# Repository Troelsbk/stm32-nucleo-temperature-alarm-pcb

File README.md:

# STM32 Nucleo Temperature Alarm

## Overview
This project demonstrates a temperature alarm system built on the STM32 Nucleo F042K6 platform with a custom PCB designed in KiCad.  
It integrates multiple I/O types, including I²C, ADC with interrupts, PWM, GPIO buttons, and LEDs.  
The system activates an alarm when the measured temperature falls below a user-defined threshold.  
A potential application is monitoring room temperature when ventilating by opening windows.

## Hardware
- STM32 Nucleo F042K6 development board  
- Custom PCB designed in KiCad  
- Analog temperature sensor TMP36  
- Digital temperature sensor TMP102  
- Push buttons for setting the threshold  
- Buzzer for alarm output  
- OLED display  
- Status LEDs  

### System Overview

### OLED
This project uses the [stm32-ssd1306] library to drive the OLED display.  
In addition, three helper functions were implemented to simplify text rendering on the OLED.  
These functions are defined in `oled_function.c`:

- `void send_strXY(char *str, uint8_t x, uint8_t y, uint8_t size);`  
- `char send_charXY(char ch, uint8_t x, uint8_t y);`  
- `void clear_oled(void);`  

### Schematic
The schematic designed in KiCad is shown below:  

### Breadboard Prototype

## Firmware
The firmware was developed using STM32CubeIDE.  
It is available in the [`stm32_firmware/`](./stm32_firmware) folder.  
To rebuild the project:  
1. Open the `.ioc` configuration file in STM32CubeMX.  
2. Regenerate the source code.  
3. Compile using STM32CubeIDE or a compatible ARM toolchain.  

## PCB
### Layout

### 3D Model

### Assembled PCB
The fully assembled PCB is shown below.  
The green LED indicates that the I²C bus is operational.  
The red LED flashes, and the buzzer sounds, when the temperature measured by the TMP102 falls below the user-defined threshold.

### PCB Performance
The analog TMP36 sensor showed a deviation of 0–3 °C above the reference, while the TMP102 measured about 1 °C higher.  
Aside from these temperature discrepancies, the PCB performed as expected.

## Demo Video

## Summary
Overall, the project achieved its primary goal of providing hands-on experience with KiCad, as well as STM32 features including ADC with interrupts, timers, I²C, PWM, GPIO, and OLED display integration.  
This made it a valuable learning and familiarization exercise with the STM32 Nucleo ecosystem.

## License
MIT License (or another license of your choice).

[stm32-ssd1306]: https://github.com/afiskon/stm32-ssd1306

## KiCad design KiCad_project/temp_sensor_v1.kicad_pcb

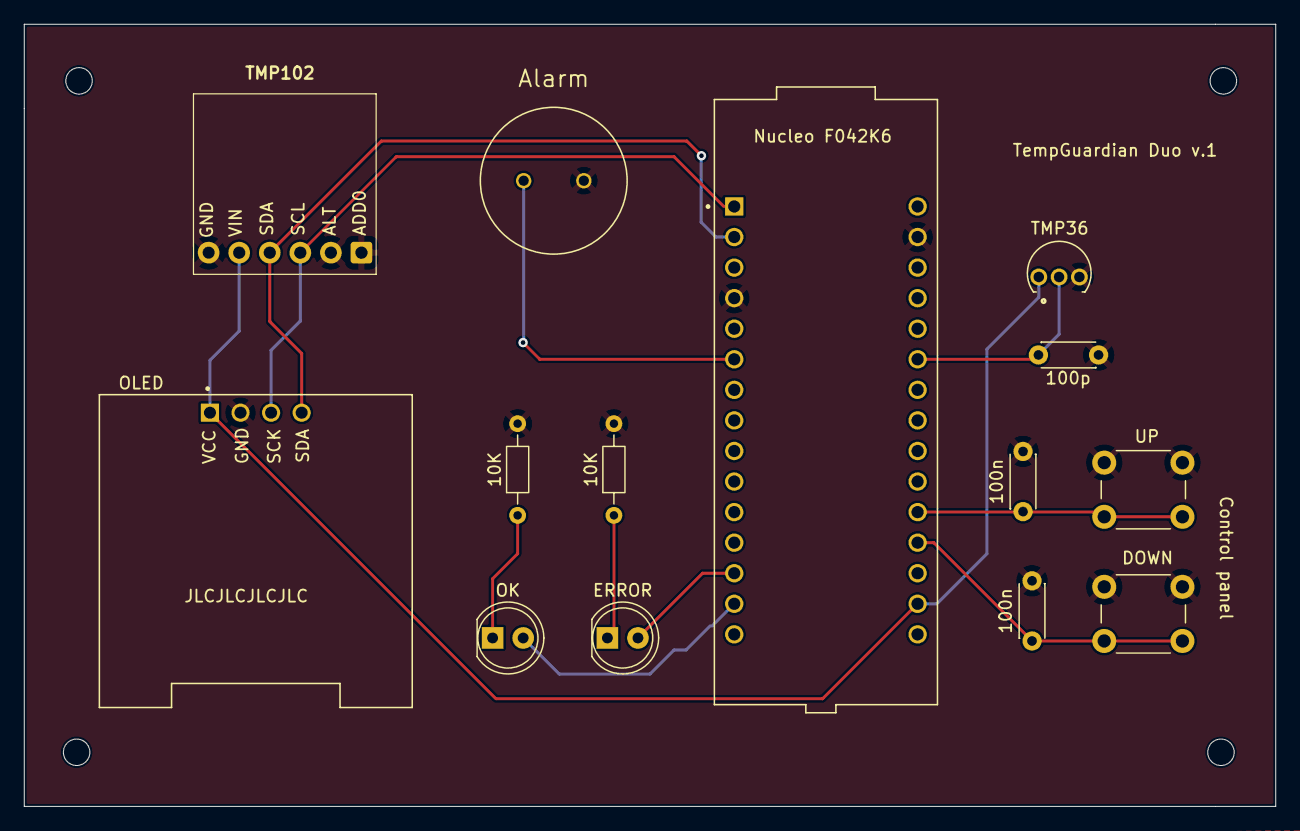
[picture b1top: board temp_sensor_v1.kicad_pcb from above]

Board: 2 copper layers, 104.0 x 65.0 mm, 14 parts (0 on the bottom side), 12 nets.

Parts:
10K, 10K#2: 10k; R_Axial_DIN0204_L3.6mm_D1.6mm_P7.62mm_Horizontal
100n, 100n#2: 100n; C_Disc_D4.3mm_W1.9mm_P5.00mm
100p: 110p; C_Disc_D4.3mm_W1.9mm_P5.00mm
Alarm: PS1240P02CT3; XDCR_PS1240P02CT3
DOWN: SW_Push; SW_PUSH_6mm
ERROR: LED; LED_D5.0mm
Nucleo F042K6: NUCLEO-F042K6; MODULE_NUCLEO-F042K6
OK: LED; LED_D5.0mm
OLED: DM-OLED096-636; MODULE_DM-OLED096-636
TMP36: TMP36_my_symbol; TMP36_custom_version
TMP102: TMP102; tmp102_custom
UP: SW_Push; SW_PUSH_6mm

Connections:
+3.3V: Nucleo F042K6.CN4_14 (+3V3), OLED.1 (GND), TMP36.1 (+VS), TMP102.2 (VCC_IN)
GND: 10K.2, 10K#2.2, 100n.2, 100n#2.2, 100p.1, Alarm.1, DOWN.1, Nucleo F042K6.CN3_4 (GND_CN3), Nucleo F042K6.CN4_2 (GND_CN4), OLED.2 (VCC_IN), TMP36.3 (GND), TMP102.1 (GND), TMP102.5 (ALT), TMP102.6 (ADD0), UP.1
unnamed: Nucleo F042K6.CN3_14 (PB5/D11), OK.2 (A)
unnamed: 10K#2.1, OK.1 (K)
unnamed: ERROR.2 (A), Nucleo F042K6.CN3_13 (PA11/D10)
unnamed: 10K.1, ERROR.1 (K)
unnamed: 100n.1, DOWN.2, Nucleo F042K6.CN4_12 (PA0/A0)
unnamed: 100n#2.1, Nucleo F042K6.CN4_11 (PA1/A1), UP.2
unnamed: 100p.2, Nucleo F042K6.CN4_6 (PA7/A6), TMP36.2 (VOUT)
unnamed: Nucleo F042K6.CN3_1 (PA9/D1), OLED.3 (SCL), TMP102.4 (SCL)
unnamed: Nucleo F042K6.CN3_2 (PA10/D0), OLED.4 (SDA), TMP102.3 (SDA)
unnamed: Alarm.2, Nucleo F042K6.CN3_6 (PB0/D3)

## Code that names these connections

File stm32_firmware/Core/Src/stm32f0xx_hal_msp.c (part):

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
    __HAL_RCC_GPIOA_CLK_ENABLE();
    /**ADC GPIO Configuration
    PA7     ------> ADC_IN7
    */
    GPIO_InitStruct.Pin = GPIO_PIN_7;
    GPIO_InitStruct.Mode = GPIO_MODE_ANALOG;
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    __HAL_RCC_ADC1_CLK_DISABLE();

    /**ADC GPIO Configuration
    PA7     ------> ADC_IN7
    */
    HAL_GPIO_DeInit(GPIOA, GPIO_PIN_7);

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
    __HAL_RCC_GPIOA_CLK_ENABLE();
    /**I2C1 GPIO Configuration
    PA9     ------> I2C1_SCL
    PA10     ------> I2C1_SDA
    */
    GPIO_InitStruct.Pin = GPIO_PIN_9|GPIO_PIN_10;
    GPIO_InitStruct.Mode = GPIO_MODE_AF_OD;
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    __HAL_RCC_I2C1_CLK_DISABLE();

    /**I2C1 GPIO Configuration
    PA9     ------> I2C1_SCL
    PA10     ------> I2C1_SDA
    */
    HAL_GPIO_DeInit(GPIOA, GPIO_PIN_9);

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
    __HAL_RCC_GPIOB_CLK_ENABLE();
    /**TIM3 GPIO Configuration
    PB0     ------> TIM3_CH3
    */
    GPIO_InitStruct.Pin = GPIO_PIN_0;
    GPIO_InitStruct.Mode = GPIO_MODE_AF_PP;
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
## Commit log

2025-08-17 Rename readme.txt to readme.txt
2025-08-17 Add firmware
2025-08-17 Add KiCad project files
2025-08-17 Add KiCad project files and firmware
2025-08-23 Add final firmware with corrected temperatures

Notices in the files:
stm32_firmware/Core/Src/stm32f0xx_hal_msp.c:
Copyright (c) 2025 STMicroelectronics.
All rights reserved.
This software is licensed under terms that can be found in the LICENSE file
